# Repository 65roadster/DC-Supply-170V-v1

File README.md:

# DC-Supply-170V-v1
 Lab supply for testing offline AC-DC converters

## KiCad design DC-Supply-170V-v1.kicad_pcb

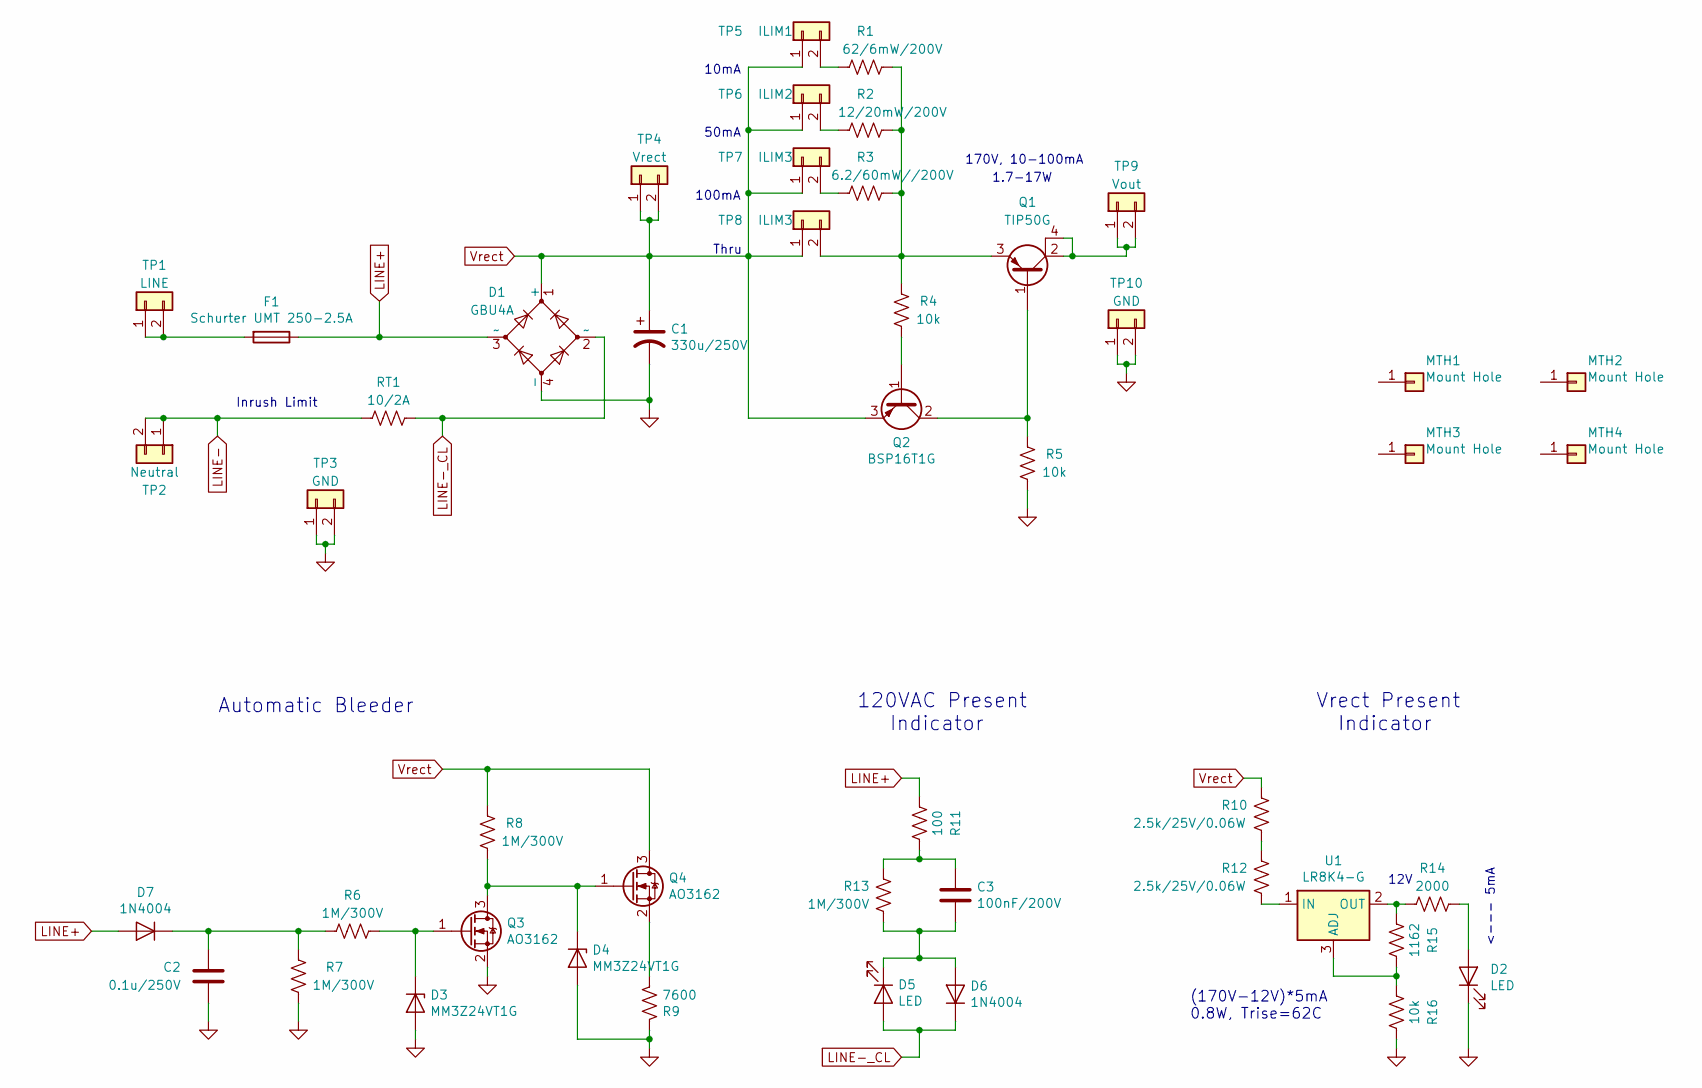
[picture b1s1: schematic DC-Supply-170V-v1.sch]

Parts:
C1: 330u/250V; Nichicon-UVR2E331MRD6-Cap-330uF-250V
C2: 0.1u/250V; C_1206_HandSoldering
C3: 100nF/200V; C_1206_HandSoldering
D1: GBU4A; GBU4A-Bridge-Rectifier
D2: LED; LED_0805_2012Metric
D3, D4: MM3Z24VT1G; D_SOD-323_HandSoldering
D5: LED; LED_0805_2012Metric_Pad1.15x1.40mm_HandSolder
D6, D7: 1N4004; D_SMA_Handsoldering
F1: Schurter UMT 250-2.5A; Schurter-0751.0110-Fuse-Clip-5mm_20mm
MTH1, MTH2, MTH3, MTH4: Mount Hole; Mount-Hole-#6
Q1: TIP50G; TO-220-3_Horizontal_Tab4
Q2: BSP16T1G; SOT-223-3_TabPin2
Q3, Q4: AO3162; SOT-23-3_HandSoldering
R1: 62/6mW/200V; R_1210_HandSoldering
R2: 12/20mW/200V; R_1210_HandSoldering
R3: 6.2/60mW//200V; R_1210_HandSoldering
R4, R5, R16: 10k; R_0805_HandSoldering
R6, R7, R8, R13: 1M/300V; R_0805_HandSoldering
R9: 7600; R_2512_HandSoldering
R10, R12: 2.5k/25V/0.06W; R_0805_HandSoldering
R11: 100; R_0805_HandSoldering
R14: 2000; R_0805_HandSoldering
R15: 1162; R_0805_HandSoldering
RT1: 10/2A; Thermistor-TDK-B5713S0xxxM0xx
TP1: LINE; Green_Terminal_Block_x02_150mil
TP2: Neutral; Green_Terminal_Block_x02_150mil
TP3: GND; PinHeader_1x02_P2.54mm_Vertical
TP4: Vrect; PinHeader_1x02_P2.54mm_Vertical
TP5: ILIM1; PinHeader_1x02_P2.54mm_Vertical
TP6: ILIM2; PinHeader_1x02_P2.54mm_Vertical
TP7, TP8: ILIM3; PinHeader_1x02_P2.54mm_Vertical
TP9: Vout; Green_Terminal_Block_x02_150mil
TP10: GND; Green_Terminal_Block_x02_150mil
U1: LR8K4-G; SOT-223-3_TabPin2

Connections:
GND: C1.2, C2.1, D1.4 (-), D2.1 (K), D3.2 (A), D4.2 (A), Q3.2 (S), R5.1, R7.2, R9.2, R16.2, TP3.1, TP3.2, TP10.1, TP10.2
LINE+: D1.3 (~~), D7.2 (A), F1.1, R11.2
LINE-: RT1.2, TP2.1, TP2.2
LINE-_CL: D1.2 (~~), D5.2 (A), D6.1 (K), RT1.1
unnamed: C2.2, D7.1 (K), R6.2, R7.1
unnamed: C3.1, R11.1, R13.1
unnamed: C3.2, D5.1 (K), D6.2 (A), R13.2
unnamed: D2.2 (A), R14.2
unnamed: D3.1 (K), Q3.1 (G), R6.1
unnamed: D4.1 (K), Q3.3 (D), Q4.1 (G), R8.1
unnamed: F1.2, TP1.1, TP1.2
unnamed: Q1.1 (B), Q2.2 (C), R5.2
unnamed: Q1.2 (C), Q1.4 (C), TP9.1, TP9.2
unnamed: Q1.3 (E), R1.2, R2.2, R3.2, R4.2, TP8.2
unnamed: Q2.1 (B), R4.1
unnamed: Q4.2 (S), R9.1
unnamed: R1.1, TP5.2
unnamed: R2.1, TP6.2
unnamed: R3.1, TP7.2
unnamed: R10.2, R12.1
unnamed: R12.2, U1.1 (IN)
unnamed: R14.1, R15.1, U1.2 (OUT)
unnamed: R15.2, R16.1, U1.3 (ADJ)
Vrect: C1.1, D1.1 (+), Q2.3 (E), Q4.3 (D), R8.2, R10.1, TP4.1, TP4.2, TP5.1, TP6.1, TP7.1, TP8.1

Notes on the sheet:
Inrush Limit
1.7-17W
170V, 10-100mA
50mA
Thru
10mA
Automatic Bleeder
100mA
120VAC Present Indicator
Vrect Present Indicator
(170V-12V)*5mA 0.8W, Trise=62C
12V
<--- 5mA

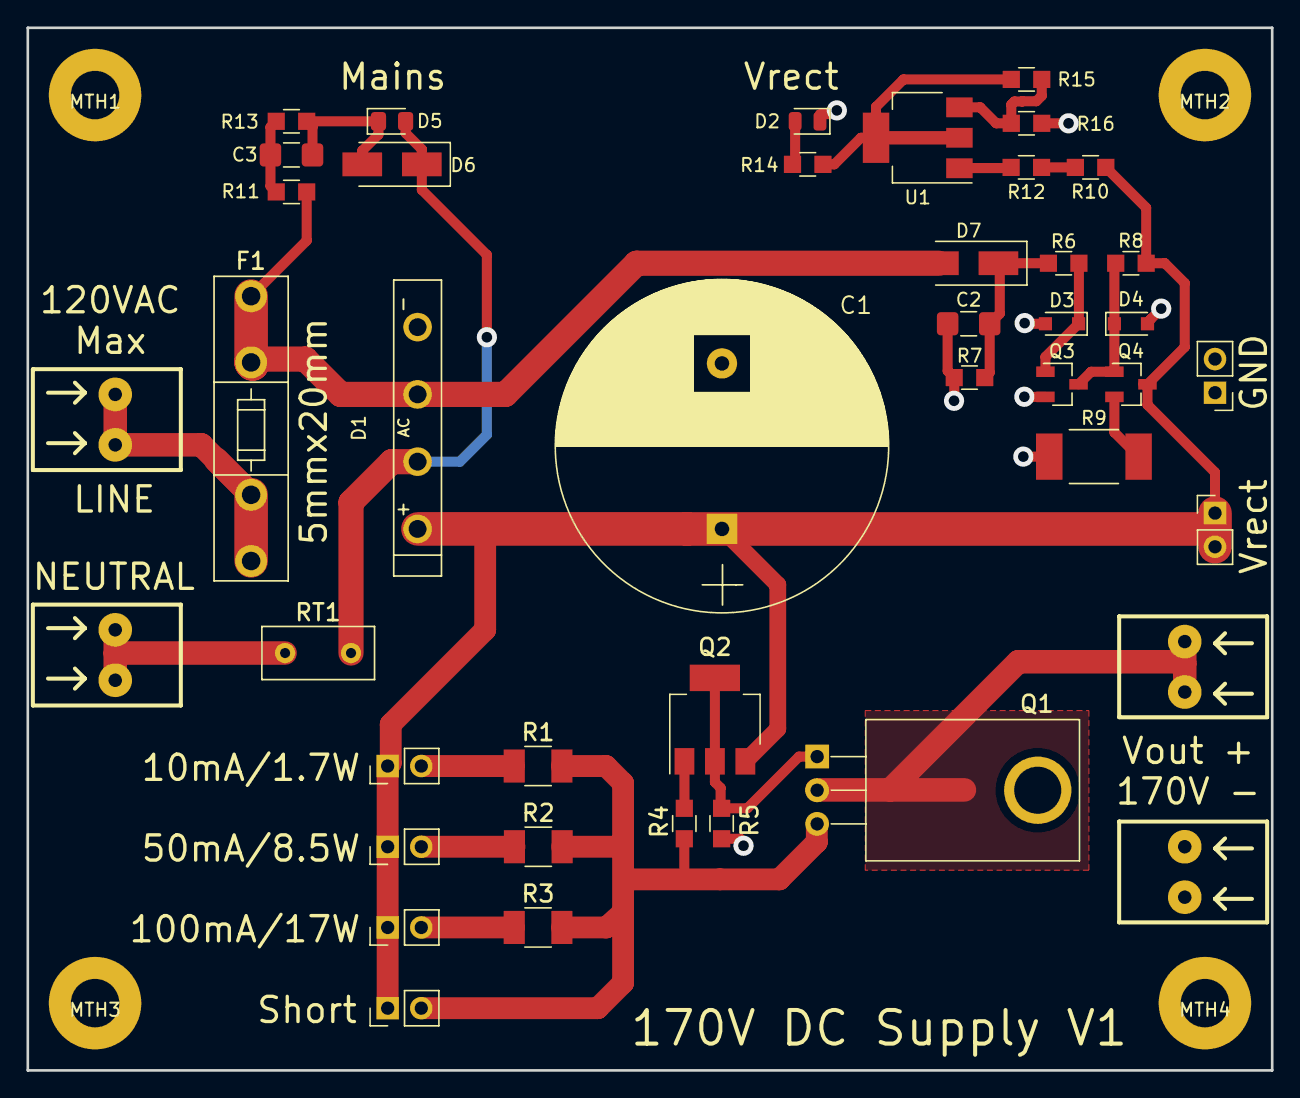
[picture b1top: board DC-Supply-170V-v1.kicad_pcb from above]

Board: 2 copper layers, 94.0 x 78.7 mm, 47 parts (0 on the bottom side), 24 nets.

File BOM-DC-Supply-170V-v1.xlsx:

170VDC Power Supply w/ Indicators
Main Circuit
Part | Qty | Description | Supplier | Link | Price ea | Extended
Fq | 2 | Fuse Holder | Digikey | https://www.digikey.com/products/en?keywords=schurter%200751.0110 | 0.14000000000000001 | 0.28000000000000003
D1 | 1 | GBU4A Bridge Rectifier | Digikey | https://www.digikey.com/products/en?x=0&y=0&lang=en&site=us&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 | 0.83 | 0.83
RT1 | 1 | Thermistor, 10 Ohm, 2A | Digikey | https://www.digikey.com/product-detail/en/epcos-tdk/B57153S0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 | 0.66 | 0.66
C1 | 1 | Capacitor, electrolytic, 330uF, 250V | Digikey | https://www.digikey.com/product-detail/en/nichicon/UVR2E331M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 | 3.75 | 3.75
R1 | 1 | Resistor, 62 Ohm, 1210, 200V | Digikey | https://www.digikey.com/product-detail/en/stackpole-electron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 | 0.11 | 0.11
R2 | 1 | Resistor, 12 Ohm, 1210, 200V | Digikey | https://www.digikey.com/product-detail/en/stackpole-electron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 | 0.11 | 0.11
R3 | 1 | Resistor, 6.2 Ohm, 1210, 200V | Digikey | https://www.digikey.com/product-detail/en/stackpole-electron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 | 0.11 | 0.11
R4 | 1 | Resistor, 10k, 0805 | Stock |  | 0 | 0
R5 | 1 | Resistor, 10k, 0805 | Stock |  | 0 | 0
Q1 | 1 | TIP50G NPN, 400V, TO-220AB | Digikey | https://www.digikey.com/product-detail/en/on-semiconductor/T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 | 0.68 | 0.68
Q2 | 1 | BSP16T1G, NPN, 100mA, 300V | Digikey | https://www.digikey.com/product-detail/en/on-semiconductor/B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 | 0.37 | 0.37
PCB | 1 | PCB | PCBWay |  |  | 1.5
 |  |  |  |  |  | 8.4
Bleeder
Q3, Q4 | 2 | AO3162, N-MOS, 34mA, 400V, SOT23 | Digikey | https://www.digikey.com/product-detail/en/alpha-omega-semico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 | 0.35 | 0.7
C2 | 1 | 0.1uF Ceramic cap, 250V | Digikey | https://www.digikey.com/product-detail/en/w-rth-elektronik/8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 | 0.17 | 0.17
R6, R7, R8 | 3 | 1M Ohm, 300V, 0805 | Digikey | https://www.digikey.com/product-detail/en/rohm-semiconductor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 | 0.14000000000000001 | 0.42000000000000004
D3, D4 | 2 | Diode, zener, 24V, 300mW, SOD-323 | Digikey | https://www.digikey.com/product-detail/en/on-semiconductor/M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 | 0.14000000000000001 | 0.28000000000000003
D7 | 1 | Diode, 1N4004 | Stock |  | 0 | 0
 |  |  |  |  |  | 0.87000000000000011
Indicators
R11 | 1 | Resistor, 100 Ohm, 0805 | Stock |  | 0 | 0
R13 | 1 | 1M Ohm, 300V, 0805 | Digikey | https://www.digikey.com/product-detail/en/rohm-semiconductor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 | 0.14000000000000001 | 0.14000000000000001
C3 | 1 | 0.1uF Ceramic cap, 250V | Digikey | https://www.digikey.com/product-detail/en/w-rth-elektronik/8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 | 0.17 | 0.17
D5 | 1 | LED, 0805 | Stock |  | 0 | 0
D6 | 1 | Diode, 1N4004 | Stock |  | 0 | 0
R10, R12 | 1 | Resistor, 2.5k, 0805 | Stock |  | 0 | 0
R14 | 1 | Resistor, 2k, 0805 | Stock |  | 0 | 0
R15 | 1 | Resistor, 1.16k, 0805 | Stock |  | 0 | 0
R16 | 1 | Resistor, 10k, 0805 | Stock |  | 0 | 0
D5 | 1 | LED, 0805 | Stock |  | 0 | 0
U1 | 1 | LR8N8-G | Digikey | https://www.digikey.com/products/en/integrated-circuits-ics/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 | 0.62 | 0.62
 |  |  |  |  |  | 0.93
 |  |  |  |  | Total | 10.200000000000001

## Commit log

2020-06-16 Layout tweaks before PCB order
2020-06-25 finalized before PCB order
